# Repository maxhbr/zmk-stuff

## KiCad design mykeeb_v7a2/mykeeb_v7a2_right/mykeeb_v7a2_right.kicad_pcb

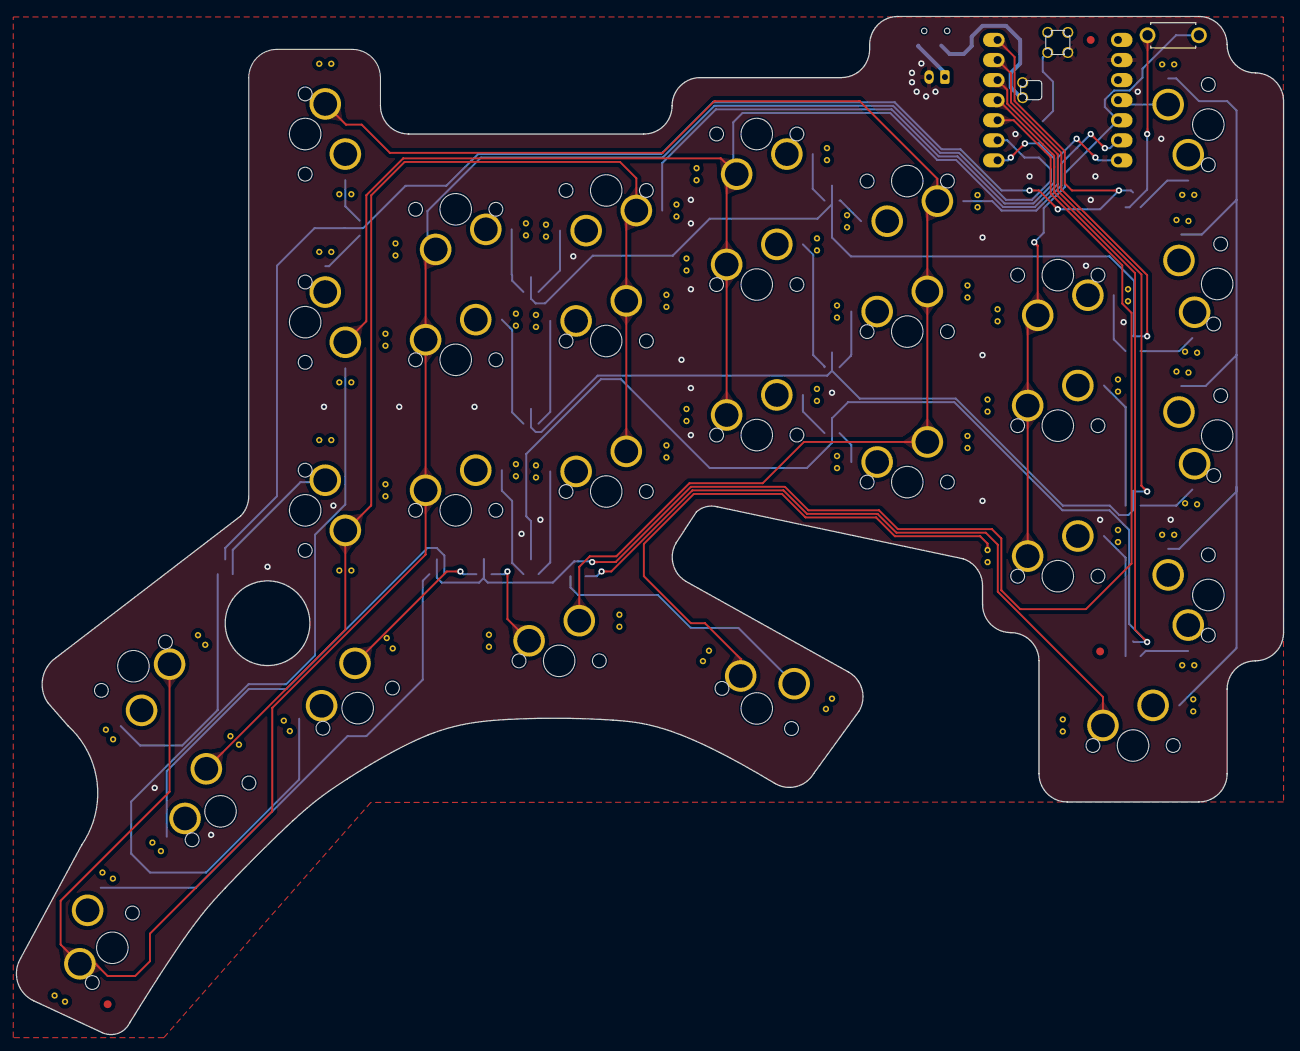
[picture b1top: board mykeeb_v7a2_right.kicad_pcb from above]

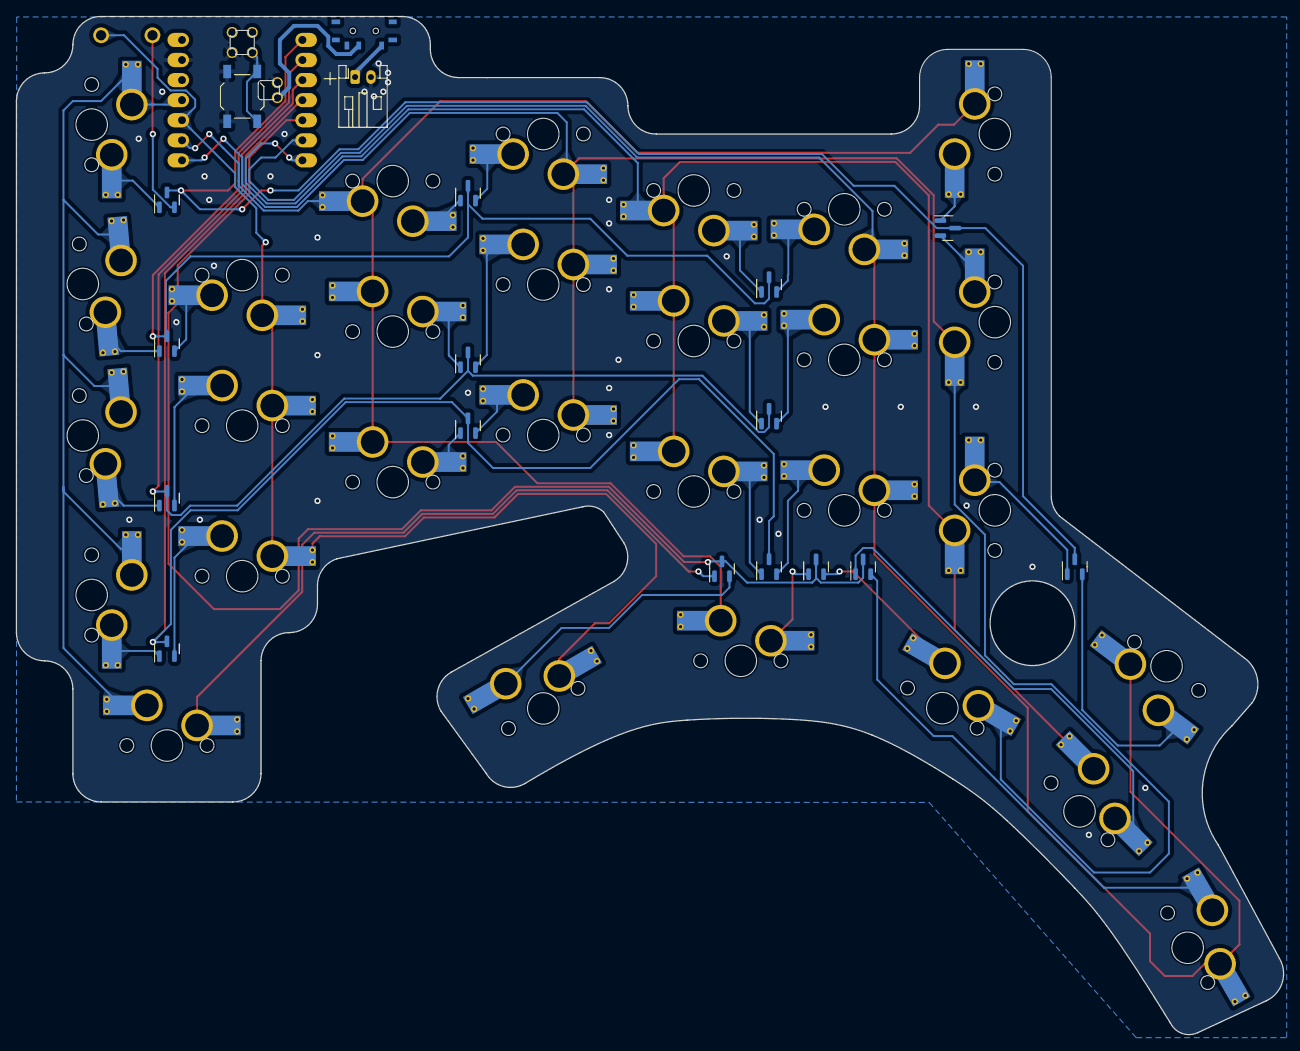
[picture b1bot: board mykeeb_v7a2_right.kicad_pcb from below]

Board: 2 copper layers, 160.4 x 128.9 mm, 52 parts (18 on the bottom side), 45 nets.

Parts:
BT1: Battery_Cell; JST_PH_S2B-PH-K_1x02_P2.00mm_Horizontal
D1, D2, D3, D4, D5, D6, D7, D8, D9, D10, D11, D12, D13, D14, D15: BAV70; SOT-23
FID1, FID2, FID3: Fiducial; Fiducial_1mm_Mask2mm
S0, S2, S3, S4, S5, S10, S11, S12, S13, S14, S15, S20, S21, S22, S23, S24, S25, S30, S31, S32, S33, S34, S35, S40, S42, S43, S44: SW; MX-1U-Hotswap
S1: SW_Push; PushSW
SW_bat1: SW_SPDT; switch-MSK-12C02-smd
SW_reset1: SW_Push; SW_SPST_TL3342
U1: xiao-ble; xiao-ble-smd-cutout
locked: SW; MX-1U-Hotswap
locked#2: SW; MX-1U-Hotswap

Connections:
BAT+: SW_bat1.2 (B), U1.19 (BAT)
COL0: S0.2, S10.2, S20.2, S30.2, S40.2, U1.11 (A6_MOSI/1.15)
COL1: S1.1, S11.2, S21.1, S31.1, U1.10 (A5_MISO/1.14), locked#2.1
COL2: S2.1, S12.1, S22.2, S32.2, S42.2, U1.9 (A7_SCK/1.13)
COL3: S3.2, S13.2, S23.1, S33.1, S43.1, U1.8 (B9_RX/1.12)
COL4: S4.2, S14.1, S24.2, S34.2, S44.2, U1.7 (B8_TX/1.11)
COL5: S5.1, S15.2, S25.1, S35.1, U1.6 (A9_SCL/0.05_H), locked.1
GND: BT1.2 (-), SW_reset1.2, U1.13 (GND), U1.18 (GND), U1.20 (GND)
unnamed: D1.1 (A1), S0.1
unnamed: D1.2 (A2), S1.2
unnamed: D2.1 (A1), S10.1
unnamed: D2.2 (A2), S11.1
unnamed: D3.1 (A1), S20.1
unnamed: D3.2 (A2), S21.2
unnamed: D4.1 (A1), S30.1
unnamed: D4.2 (A2), S31.2
unnamed: D5.1 (A1), S40.1
unnamed: D5.2 (A2), locked#2.2
unnamed: D6.1 (A1), S2.2
unnamed: D6.2 (A2), S3.1
unnamed: D7.1 (A1), S12.2
unnamed: D7.2 (A2), S13.1
unnamed: D8.1 (A1), S22.1
unnamed: D8.2 (A2), S23.2
unnamed: D9.1 (A1), S32.1
unnamed: D9.2 (A2), S33.2
unnamed: D10.1 (A1), S42.1
unnamed: D10.2 (A2), S43.2
unnamed: D11.1 (A1), S4.1
unnamed: D11.2 (A2), S5.2
unnamed: D12.1 (A1), S14.2
unnamed: D12.2 (A2), S15.1
unnamed: D13.1 (A1), S24.1
unnamed: D13.2 (A2), S25.2
unnamed: D14.1 (A1), S34.1
unnamed: D14.2 (A2), S35.2
unnamed: D15.1 (A1), S44.1
unnamed: D15.2 (A2), locked.2
RESET: SW_reset1.1, U1.17 (RESET)
ROW0: D1.3 (K), D6.3 (K), D11.3 (K), U1.1 (A2/0.02_H)
ROW1: D2.3 (K), D7.3 (K), D12.3 (K), U1.2 (A4/0.03_H)
ROW2: D3.3 (K), D8.3 (K), D13.3 (K), U1.3 (A10/0.28)
ROW3: D4.3 (K), D9.3 (K), D14.3 (K), U1.4 (A11/0.29)
ROW4: D5.3 (K), D10.3 (K), D15.3 (K), U1.5 (A8_SDA/0.04_H)
VBAT: BT1.1 (+), SW_bat1.1 (A)
